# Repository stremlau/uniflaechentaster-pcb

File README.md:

# uniflaechentaster-pcb
PCB for the Uniflächentaster (http://uniflaechentaster.de)

* Si7021 sensor for temperature and humidity
* ATSHA chip for signed communication
* one micro-switch
* possibility to wire the two switches from the Uniflächentaster
* CR2032 battery powered

Images of the PCB at https://www.openhardware.io/view/419

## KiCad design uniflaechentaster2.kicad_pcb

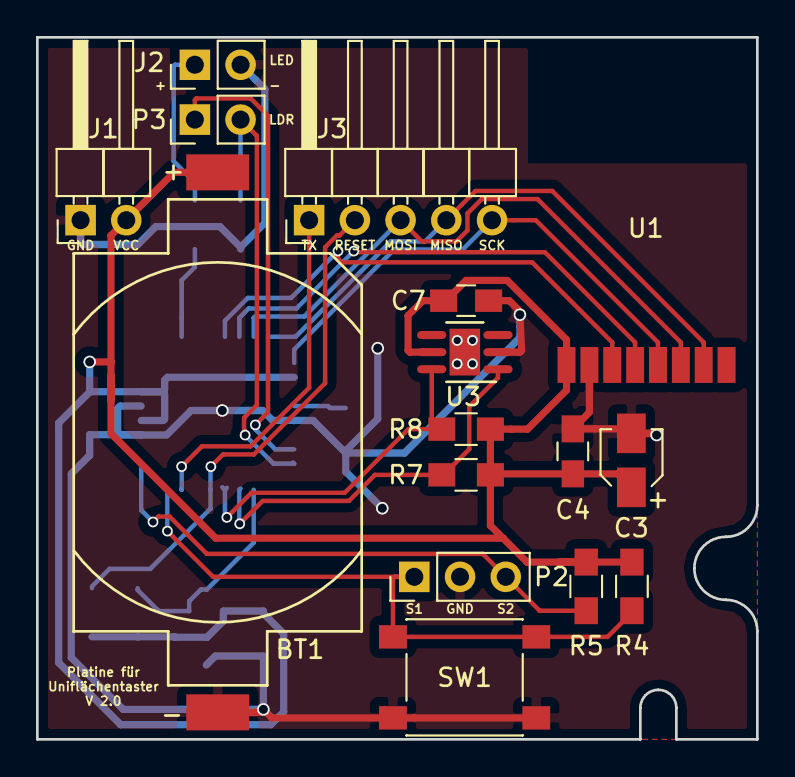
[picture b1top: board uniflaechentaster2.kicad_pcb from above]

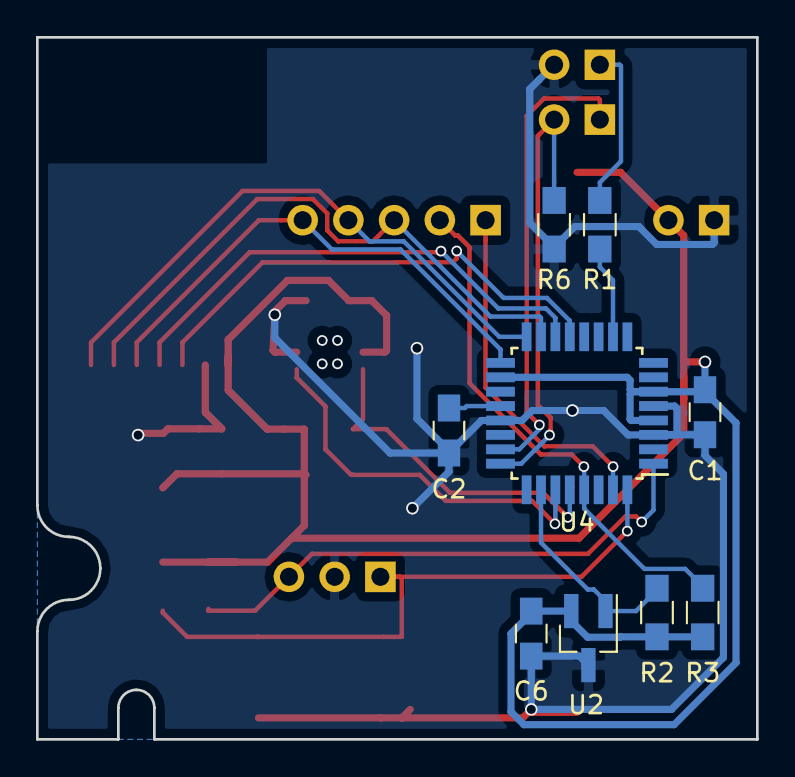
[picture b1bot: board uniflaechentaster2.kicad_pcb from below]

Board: 2 copper layers, 40.0 x 39.0 mm, 25 parts (9 on the bottom side), 19 nets.

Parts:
BT1: Battery_Cell; CR2032-battery-holder
C1, C2, C4, C6, C7: 100nF; C_0805_HandSoldering
C3: 4.7uF; CP_Elec_3x5.3
J1: Power; Pin_Header_Angled_1x02_Pitch2.54mm
J2: LED; Pin_Header_Straight_1x02_Pitch2.54mm
J3: ISP and TX; Pin_Header_Angled_1x05_Pitch2.54mm
P2: Switches; Pin_Header_Straight_1x03_Pitch2.54mm
P3: LDR; Pin_Header_Straight_1x02_Pitch2.54mm
R1: 220; R_0805_HandSoldering
R2, R3, R4, R5, R6, R7, R8: 10k; R_0805_HandSoldering
SW1: SW_DIP_x01; SW_SPST_PTS645
U1: NRF24L01; NRF24L01-SMD
U2: ATSHA204A; SOT-23_Handsoldering
U3: Si7021; DFN-6-1EP_3x3mm_Pitch0.95mm
U4: ATMEGA328P-AU; TQFP-32_7x7mm_Pitch0.8mm

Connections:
/ATSHA_SDA: R2.1, U2.1, U4.26
/CE: U1.3, U4.13
/CSN: U1.4, U4.14
/LDR_IN: P3.2, R6.2, U4.24
/LDR_VCC: P3.1, U4.23
/MISO: J3.4, U1.7, U4.16
/MOSI: J3.3, U1.6, U4.15
/RESET: J3.2, R3.2, U4.29
/S1: P2.1, R4.2, SW1.1, U4.32
/S2: P2.3, R5.2, U4.1
/SCK: J3.5, U1.5, U4.17
/SCL: R8.2, U3.6, U4.28
/SDA: R7.2, U3.1, U4.27
/TX: J3.1, U4.31
GND: BT1.2, C1.2, C2.2, C3.2, C4.2, C6.2, C7.2, J1.1, J2.2, P2.2, R6.1, SW1.2, U1.1, U2.3, U3.2, U4.3, U4.5, U4.21
unnamed: C2.1, U4.20
unnamed: J2.1, R1.1
unnamed: R1.2, U4.10
VCC: BT1.1, C1.1, C3.1, C4.1, C6.1, C7.1, J1.2, R2.2, R3.1, R4.1, R5.1, R7.1, R8.1, U1.2, U2.2, U3.5, U4.4, U4.6, U4.18

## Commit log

2017-07-02 working version 2.0
2017-07-02 Create LICENSE
